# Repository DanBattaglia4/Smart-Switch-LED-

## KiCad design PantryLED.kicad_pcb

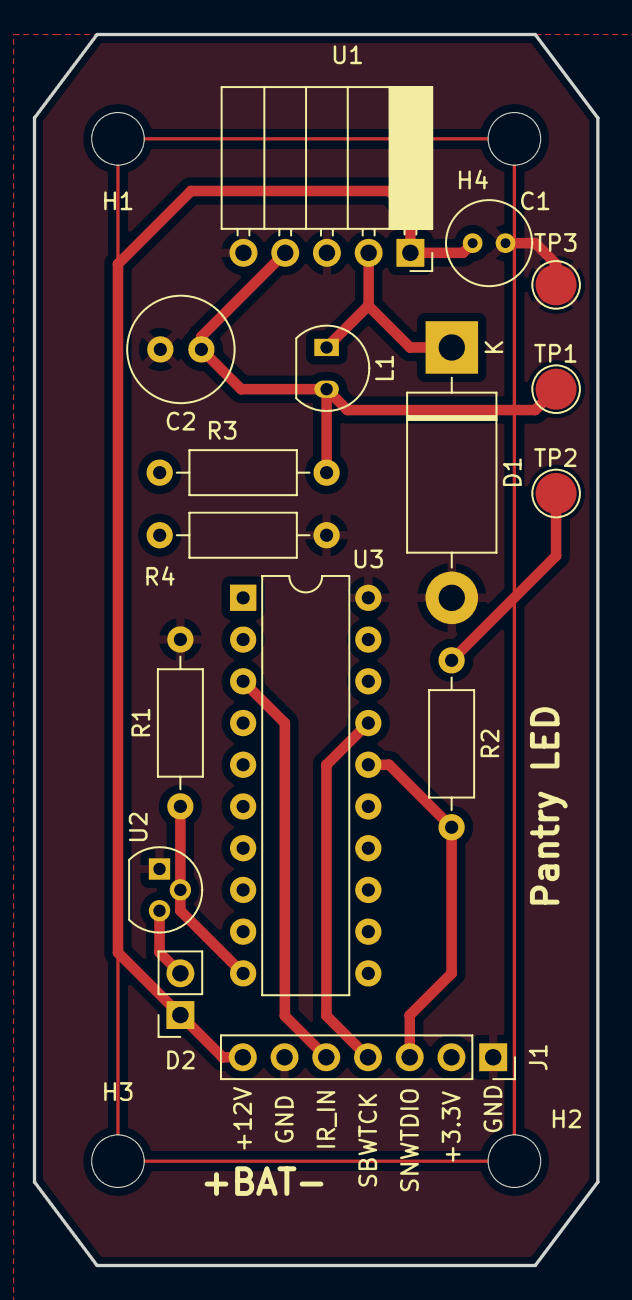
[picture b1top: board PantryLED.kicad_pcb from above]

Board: 2 copper layers, 34.3 x 74.9 mm, 20 parts (0 on the bottom side), 10 nets.

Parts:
C1: 100u; C_Radial_D5.0mm_H7.0mm_P2.00mm
C2: 1000u; C_Radial_D6.3mm_H5.0mm_P2.50mm
D1: 1N5822; D_DO-201AD_P15.24mm_Horizontal
D2: LED; PinSocket_1x02_P2.54mm_Vertical
H1, H2, H3, H4: MountingHole; MountingHole_3.2mm_M3
J1: Conn_01x06_Male; PinSocket_1x07_P2.54mm_Vertical
L1: 100u; TO-92-2
R1, R2: 1k; R_Axial_DIN0207_L6.3mm_D2.5mm_P10.16mm_Horizontal
R3: 2k; R_Axial_DIN0207_L6.3mm_D2.5mm_P10.16mm_Horizontal
R4: 4k; R_Axial_DIN0207_L6.3mm_D2.5mm_P10.16mm_Horizontal
TP1: 5V Rail; TestPoint_Pad_D2.5mm
TP2: 3.3V Rail; TestPoint_Pad_D2.5mm
TP3: GND; TestPoint_Pad_D2.5mm
U1: LM2576HVS-3.3; PinSocket_1x05_P2.54mm_Horizontal
U2: VN2106N3-G; TO-92
U3: MSP430G2202IN20; DIP-20_W7.62mm

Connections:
+3.3V: J1.2, R2.1, R3.2, R4.1, TP2.1, U3.1 (DVCC)
+5V: C2.1, L1.2, R3.1, TP1.1, U1.4 (FB)
+12V: C1.1, D2.1 (K), J1.7, U1.1 (VIN)
GND: C1.2, C2.2, D1.2 (A), J1.1, J1.6, R1.2, R4.2, TP3.1, U1.3 (GND), U1.5 (~ON/OFF), U2.1 (S), U3.20 (DVSS)
unnamed: D1.1 (K), L1.1, U1.2 (OUT)
unnamed: D2.2 (A), U2.3 (D)
unnamed: R1.1, U2.2 (G), U3.10 (P2.2)
unnamed: J1.5, U3.3 (TA0.0/P1.1)
SBWTCK: J1.4, U3.17 (SBWTCK/TEST)
SBWTDIO: J1.3, R2.2, U3.16 (~RST/NMI/SBWTDIO)

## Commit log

2024-08-25 adding files
    adding files
    git push
2024-09-05 put back R2
